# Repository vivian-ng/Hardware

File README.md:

# Hardware

Repository of all hardware related files, including schematics, gerber files, and related software.

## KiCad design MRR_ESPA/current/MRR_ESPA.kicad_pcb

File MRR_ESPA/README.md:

# MRR ESPA
## A basic 3D printer control board based on ESP32

This is a bare-minimum 3D printer control board based on the ESP32 microcontroller, which comes with built-in WiFi and BlueTooth.

**Work in progress! Do not attempt production using this schematic!**<br>
**Current version: v1.0**<br>
Note: As of v0.8, files have been migrated to KiCad so that the files can be more accessible to everyone who wishes to modify them.<br>

Features:
- Able to use up to 4 stepper drivers: X, Y, Z, and E0
- 12V to 24V input power supply
- Separate power supply for the heat bed
- X, Y, and Z min endstops
- Allows the use of a Z-axis probe, such as an inductive sensor, running on the input supply voltage (12V to 24V)
- AUX1 connector for use with an external host, such as the closed-source MKS TFT32 (**Untested!!**)
- Physical size of 99.5mm by 99.5mm. Mounting holes are 3.5mm in diameter, with centers 4mm from the edges.
- "BOOT" button can be used to reset the board.

# Firmware

Marlin 2.0 has added support for ESP32. This board was based on the initial pins definition used. <br>
In addition, [Luc](https://github.com/luc-github) has been working on a Marlin fork which incorporates part of his ESP3D webUI into Marlin itself.

## Flashing firmware

- You should be able to flash firmware through the USB port. Depending on your operating system, you may need to install drivers for the CH340. Please use Google or another search engine to find the right CH340 driver for your operating system.
- To flash firmware by directly connecting to TX/RX pins, you will need to connect IO0 to GND, then reboot (press "BOOT" button) to enter flash mode. After flashing the firmware, disconnect IO0 from GND, and press "BOOT" button again to reboot into normal mode.
- Use a baud rate of 115200.

# Pins

To be added

# License
Released under CERN Open Hardware Licence v1.2. See LICENSE.txt for details.

## Warning

- This product uses high currents which may cause fires. Use with caution.
- Do not use input voltages higher than 24V. Input current must not exceed 15A.
- Do not attempt to use more than 15A for the heated bed. While the MOSFET is capable of such currents, the connectors are not. If you need more than 15A, use an external MOSFET. In any case, it is highly recommended to use an external MOSFET for the heated bed to avoid drawing high currents through this product.
- Do not attempt to use more than 5A for the hot end. While the MOSFET is capable of such currents, the connectors are not. If you need more than 5A, use an external MOSFET.
- Do not reverse polarity.
- The breakout and endstop pins are rated for 3.3V, which is the voltage the ESP32 operates at. Attempting to feed inputs above 3.3V to these pins may damage the board.
- It is recommended to power the board only via USB (i.e. turn off PSU power supply) when flashing the board.

## Disclaimer

This product is provided as-is. While care has been taken to design a safe product, it is the user's responsibility to make sure precautions are taken to prevent damage or injury when using this product. This includes adhering to all warnings provided. By using this product, the user accepts responsibility to bear all liabilities from any damage or injury arising from the use of this product.

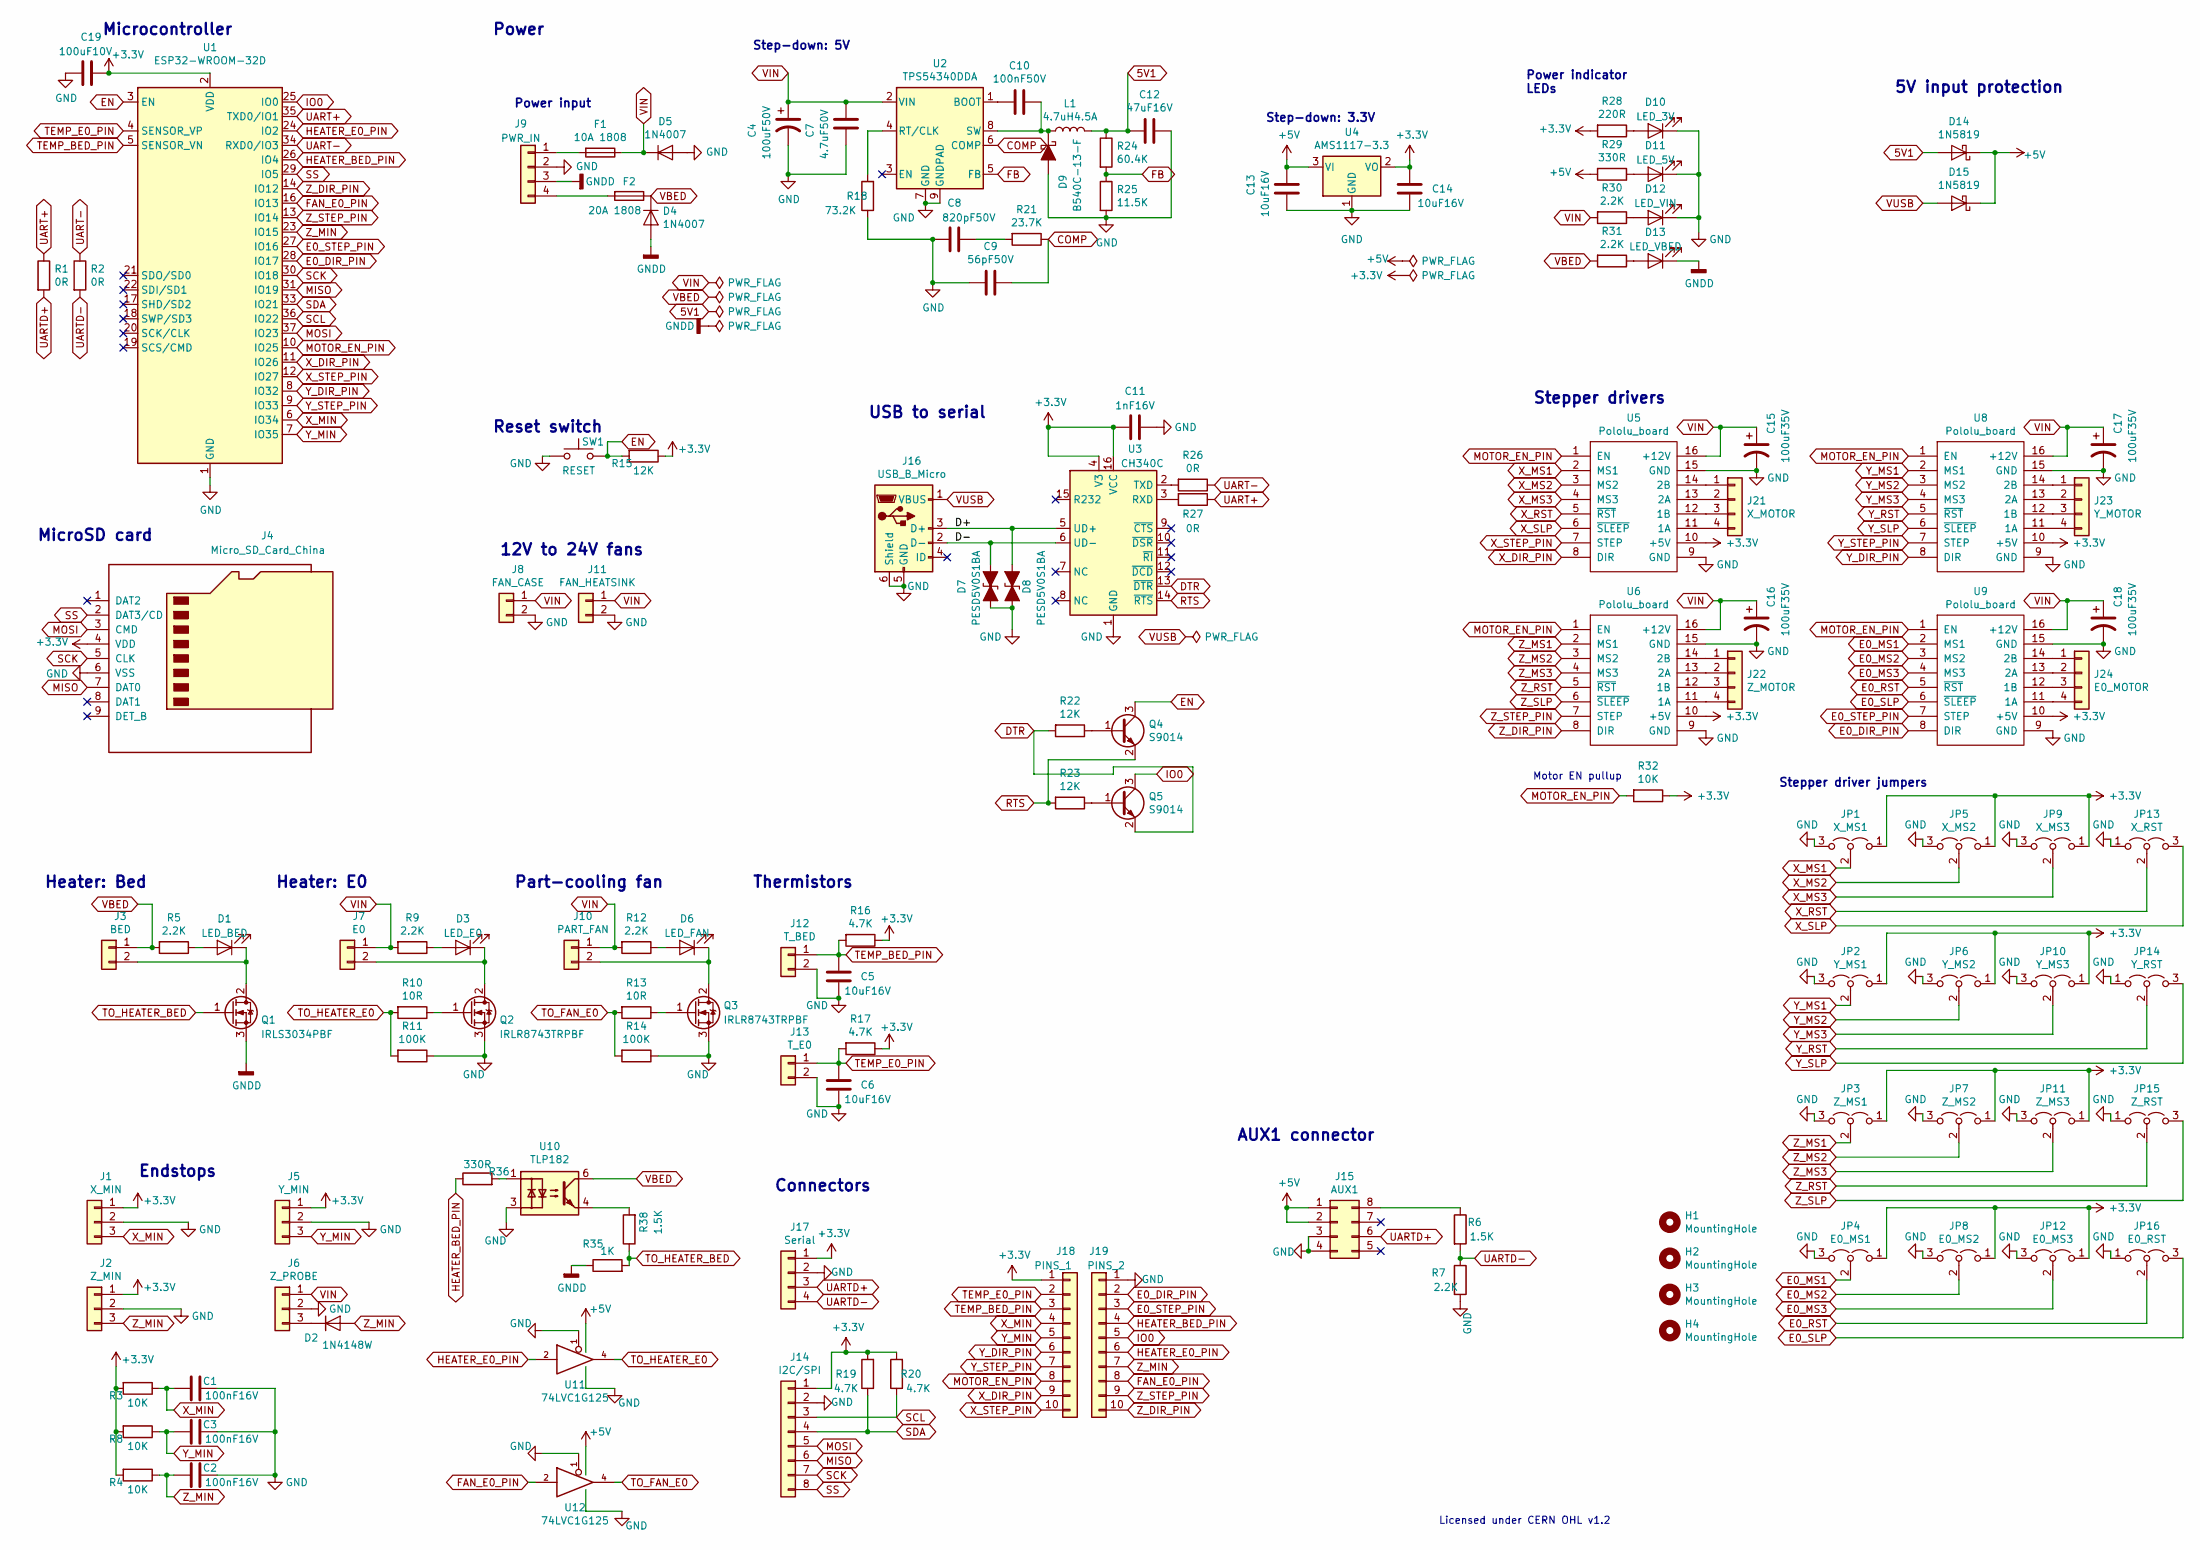
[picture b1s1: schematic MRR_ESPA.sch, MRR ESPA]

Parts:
C1, C2, C3: 100nF16V; C_0805_2012Metric
C4: 100uF50V; CP_Elec_8x10
C5, C6, C13, C14: 10uF16V; C_0805_2012Metric
C7: 4.7uF50V; C_1206_3216Metric
C8: 820pF50V; C_0805_2012Metric
C9: 56pF50V; C_0805_2012Metric
C10: 100nF50V; C_0805_2012Metric
C11: 1nF16V; C_0805_2012Metric
C12: 47uF16V; C_1206_3216Metric
C15, C16, C17, C18: 100uF35V; CP_Elec_6.3x7.7
C19: 100uF10V; C_1206_3216Metric
D1: LED_BED; LED_0805
D2: 1N4148W; D_SOD-123
D3: LED_E0; LED_0805
D4, D5: 1N4007; D_SOD-123F
D6: LED_FAN; LED_0805
D7, D8: PESD5V0S1BA; D_SOD-323
D9: B540C-13-F; D_SMC
D10: LED_3V; LED_0805
D11: LED_5V; LED_0805
D12: LED_VIN; LED_0805
D13: LED_VBED; LED_0805
D14, D15: 1N5819; D_SOD-123
F1: 10A 1808; Littelfuse_0451
F2: 20A 1808; Littelfuse_0451
H1, H2, H3, H4: MountingHole; MountingHole_3.2mm_M3_DIN965
J1: X_MIN; PinHeader_1x03_P2.54mm_Vertical
J2: Z_MIN; PinHeader_1x03_P2.54mm_Vertical
J3: BED; TerminalBlock_Phoenix_MKDS-3-2-5.08_1x02_P5.08mm_Horizontal
J4: Micro_SD_Card_China; Conn_uSDcard
J5: Y_MIN; PinHeader_1x03_P2.54mm_Vertical
J6: Z_PROBE; PinHeader_1x03_P2.54mm_Vertical
J7: E0; TerminalBlock_Phoenix_MKDS-1,5-2-5.08_1x02_P5.08mm_Horizont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
J8: FAN_CASE; PinHeader_1x02_P2.54mm_Vertical
J9: PWR_IN; TerminalBlock_Phoenix_MKDS-3-4-5.08_1x04_P5.08mm_Horizontal
J10: PART_FAN; PinHeader_1x02_P2.54mm_Vertical
J11: FAN_HEATSINK; PinHeader_1x02_P2.54mm_Vertical
J12: T_BED; PinHeader_1x02_P2.54mm_Vertical
J13: T_E0; PinHeader_1x02_P2.54mm_Vertical
J14: I2C/SPI; PinHeader_1x08_P2.54mm_Vertical
J15: AUX1; IDC-Header_2x04_P2.54mm_Vertical
J16: USB_B_Micro; USB_Micro-B_Molex-105017-0001
J17: Serial; PinHeader_1x04_P2.54mm_Vertical
J18: PINS_1; PinHeader_1x10_P2.54mm_Vertical
J19: PINS_2; PinHeader_1x10_P2.54mm_Vertical
J21: X_MOTOR; PinHeader_1x04_P2.54mm_Vertical
J22: Z_MOTOR; PinHeader_1x04_P2.54mm_Vertical
J23: Y_MOTOR; PinHeader_1x04_P2.54mm_Vertical
J24: E0_MOTOR; PinHeader_1x04_P2.54mm_Vertical
JP1: X_MS1; PinHeader_1x03_P2.54mm_Vertical
JP2: Y_MS1; PinHeader_1x03_P2.54mm_Vertical
JP3: Z_MS1; PinHeader_1x03_P2.54mm_Vertical
JP4: E0_MS1; PinHeader_1x03_P2.54mm_Vertical
JP5: X_MS2; PinHeader_1x03_P2.54mm_Vertical
JP6: Y_MS2; PinHeader_1x03_P2.54mm_Vertical
JP7: Z_MS2; PinHeader_1x03_P2.54mm_Vertical
JP8: E0_MS2; PinHeader_1x03_P2.54mm_Vertical
JP9: X_MS3; PinHeader_1x03_P2.54mm_Vertical
JP10: Y_MS3; PinHeader_1x03_P2.54mm_Vertical
JP11: Z_MS3; PinHeader_1x03_P2.54mm_Vertical
JP12: E0_MS3; PinHeader_1x03_P2.54mm_Vertical
JP13: X_RST; PinHeader_1x03_P2.54mm_Vertical
JP14: Y_RST; PinHeader_1x03_P2.54mm_Vertical
JP15: Z_RST; PinHeader_1x03_P2.54mm_Vertical
JP16: E0_RST; PinHeader_1x03_P2.54mm_Vertical
L1: 4.7uH4.5A; SMMS0530
Q1: IRLS3034PBF; TO-263-2
Q2, Q3: IRLR8743TRPBF; TO-252-2
Q4, Q5: S9014; SOT-23
R1, R2, R26, R27: 0R; R_0805_2012Metric
R3, R4, R8, R32: 10K; R_0805_2012Metric
R5, R7, R9, R12, R30, R31: 2.2K; R_0805_2012Metric
R6, R38: 1.5K; R_0805_2012Metric
R10, R13: 10R; R_0805_2012Metric
R11, R14: 100K; R_0805_2012Metric
R15, R22, R23: 12K; R_0805_2012Metric
R16, R17, R19, R20: 4.7K; R_0805_2012Metric
R18: 73.2K; R_0805_2012Metric
R21: 23.7K; R_0805_2012Metric
R24: 60.4K; R_0805_2012Metric
R25: 11.5K; R_0805_2012Metric
R28: 220R; R_0805_2012Metric
R29, R36: 330R; R_0805_2012Metric
R35: 1K; R_0805_2012Metric
SW1: RESET; 6x6mmTactileSwitch
U1: ESP32-WROOM-32D; ESP32-WROOM-32
U2: TPS54340DDA; TI_SO-PowerPAD-8_ThermalVias
U3: CH340C; SOIC-16_3.9x9.9mm_P1.27mm
U4: AMS1117-3.3; SOT-223-3_TabPin2
U5, U6, U8, U9: Pololu_board; Pololu_Breakout-16_15.2x20.3mm
U10: TLP182; MFSOP6-4_4.4x3.6mm_P1.27mm
U11, U12: 74LVC1G125; SOT-353_SC-70-5

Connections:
5V1: C12.2, D14.2 (A), L1.2, R24.1
+3V3: C11.2, C14.1, C19.1, J1.1, J2.1, J4.4 (VDD), J5.1, J14.1, J17.1, J18.1, JP1.1 (A), JP2.1 (A), JP3.1 (A), JP4.1 (A), JP5.1 (A), JP6.1 (A), JP7.1 (A), JP8.1 (A), JP9.1 (A), JP10.1 (A), JP11.1 (A), JP12.1 (A), R3.2, R4.2, R8.2, R15.1, R16.1, R17.1, R19.2, R20.2, R28.2, R32.1, U1.2 (VDD), U3.4 (V3), U3.16 (VCC), U4.2 (VO), U5.10 (+5V), U6.10 (+5V), U8.10 (+5V), U9.10 (+5V)
+5V: C13.1, D14.1 (K), D15.1 (K), J15.1, J15.2, R29.2, U4.3 (VI), U11.5 (VCC), U12.5 (VCC)
/D+: D8.1 (A1), J16.3 (D+), U3.5 (UD+)
/D-: D7.1 (A1), J16.2 (D-), U3.6 (UD-)
COMP: C9.1, R21.1, U2.6 (COMP)
DTR: Q5.2 (E), R22.2, U3.13 (~DTR)
E0_DIR_PIN: J19.2, U1.28 (IO17), U9.8 (DIR)
E0_MS1: JP4.2 (C), U9.2 (MS1)
E0_MS2: JP8.2 (C), U9.3 (MS2)
E0_MS3: JP12.2 (C), U9.4 (MS3)
E0_RST: JP16.2 (C), U9.5 (~RST)
E0_SLP: JP16.3 (B), U9.6 (~SLEEP)
E0_STEP_PIN: J19.3, U1.27 (IO16), U9.7 (STEP)
EN: Q4.3 (C), R15.2, SW1.2, U1.3 (EN)
FAN_E0_PIN: J19.8, U1.16 (IO13), U12.2
FB: R24.2, R25.1, U2.5 (FB)
GND: C1.1, C2.1, C3.1, C4.2, C5.1, C6.1, C7.1, C8.2, C9.2, C11.1, C12.1, C13.2, C14.2, C15.2, C16.2, C17.2, C18.2, C19.2, D5.2 (A), D7.2 (A2), D8.2 (A2), D9.2 (A), D10.1 (K), D11.1 (K), D12.1 (K), J1.2, J2.2, J4.6 (VSS), J5.2, J6.2, J8.2, J9.2, J11.2, J12.2, J13.2, J14.2, J15.3, J15.4, J16.5 (GND), J16.6 (Shield), J17.2, J19.1, JP1.3 (B), JP2.3 (B), JP3.3 (B), JP4.3 (B), JP5.3 (B), JP6.3 (B), JP7.3 (B), JP8.3 (B), JP9.3 (B), JP10.3 (B), JP11.3 (B), JP12.3 (B), JP13.1 (A), JP14.1 (A), JP15.1 (A), JP16.1 (A), Q2.3 (S), Q3.3 (S), R7.2, R11.1, R14.1, R18.1, R25.2, SW1.1, U1.1 (GND), U1.15 (GND), U1.38 (GND), U1.39, U2.7 (GND), U2.9 (GNDPAD), U3.1 (GND), U4.1 (GND), U5.9 (GND), U5.15 (GND), U6.9 (GND), U6.15 (GND), U8.9 (GND), U8.15 (GND), U9.9 (GND), U9.15 (GND), U10.3, U11.1, U11.3 (GND), U12.1, U12.3 (GND)
GNDD: D4.2 (A), D13.1 (K), J9.3, Q1.3 (S), R35.1
HEATER_BED_PIN: J19.4, R36.1, U1.26 (IO4)
HEATER_E0_PIN: J19.6, U1.24 (IO2), U11.2
IO0: J19.5, Q5.3 (C), U1.25 (IO0)
MISO: J4.7 (DAT0), J14.6, U1.31 (IO19)
MOSI: J4.3 (CMD), J14.5, U1.37 (IO23)
MOTOR_EN_PIN: J18.8, R32.2, U1.10 (IO25), U5.1 (EN), U6.1 (EN), U8.1 (EN), U9.1 (EN)
unnamed: C8.1, R21.2
unnamed: C10.1, D9.1 (K), L1.1, U2.8 (SW)
unnamed: C10.2, U2.1 (BOOT)
unnamed: D1.1 (K), J3.2, Q1.2 (D)
unnamed: D1.2 (A), R5.1
unnamed: D2.1 (K), J6.3
unnamed: D3.1 (K), J7.2, Q2.2 (D)
unnamed: D3.2 (A), R9.1
unnamed: D6.1 (K), J10.2, Q3.2 (D)
unnamed: D6.2 (A), R12.1
unnamed: D10.2 (A), R28.1
unnamed: D11.2 (A), R29.1
unnamed: D12.2 (A), R30.1
unnamed: D13.2 (A), R31.1
unnamed: F1.2, J9.1
unnamed: F2.2, J9.4
unnamed: J15.8, R6.1
unnamed: J21.1, U5.14 (2B)
unnamed: J21.2, U5.13 (2A)
unnamed: J21.3, U5.12 (1B)
unnamed: J21.4, U5.11 (1A)
unnamed: J22.1, U6.14 (2B)
unnamed: J22.2, U6.13 (2A)
unnamed: J22.3, U6.12 (1B)
unnamed: J22.4, U6.11 (1A)
unnamed: J23.1, U8.14 (2B)
unnamed: J23.2, U8.13 (2A)
unnamed: J23.3, U8.12 (1B)
unnamed: J23.4, U8.11 (1A)
unnamed: J24.1, U9.14 (2B)
unnamed: J24.2, U9.13 (2A)
unnamed: J24.3, U9.12 (1B)
unnamed: J24.4, U9.11 (1A)
unnamed: Q2.1 (G), R10.1
unnamed: Q3.1 (G), R13.1
unnamed: Q4.1 (B), R22.1
unnamed: Q5.1 (B), R23.1
unnamed: R18.2, U2.4 (RT/CLK)
unnamed: R26.2, U3.2 (TXD)
unnamed: R27.2, U3.3 (RXD)
unnamed: R36.2, U10.1
unnamed: R38.2, U10.4
RTS: Q4.2 (E), R23.2, U3.14 (~RTS)
SCK: J4.5 (CLK), J14.7, U1.30 (IO18)
SCL: J14.3, R20.1, U1.36 (IO22)
SDA: J14.4, R19.1, U1.33 (IO21)
SS: J4.2 (DAT3/CD), J14.8, U1.29 (IO5)
TEMP_BED_PIN: C5.2, J12.1, J18.3, R16.2, U1.5 (SENSOR_VN)
TEMP_E0_PIN: C6.2, J13.1, J18.2, R17.2, U1.4 (SENSOR_VP)
TO_FAN_E0: R13.2, R14.2, U12.4
TO_HEATER_BED: Q1.1 (G), R35.2, R38.1
TO_HEATER_E0: R10.2, R11.2, U11.4
UART+: R1.1, R27.1, U1.35 (TXD0/IO1)
UART-: R2.1, R26.1, U1.34 (RXD0/IO3)
UARTD+: J15.6, J17.3, R1.2
UARTD-: J17.4, R2.2, R6.2, R7.1
VBED: D4.1 (K), F2.1, J3.1, R5.2, R31.2, U10.6
VIN: C4.1, C7.2, C15.1, C16.1, C17.1, C18.1, D5.1 (K), F1.1, J6.1, J7.1, J8.1, J10.1, J11.1, R9.2, R12.2, R30.2, U2.2 (VIN), U5.16 (+12V), U6.16 (+12V), U8.16 (+12V), U9.16 (+12V)
VUSB: D15.2 (A), J16.1 (VBUS)
X_DIR_PIN: J18.9, U1.11 (IO26), U5.8 (DIR)
X_MIN: C1.2, J1.3, J18.4, R3.1, U1.6 (IO34)
X_MS1: JP1.2 (C), U5.2 (MS1)
X_MS2: JP5.2 (C), U5.3 (MS2)
X_MS3: JP9.2 (C), U5.4 (MS3)
X_RST: JP13.2 (C), U5.5 (~RST)
X_SLP: JP13.3 (B), U5.6 (~SLEEP)
X_STEP_PIN: J18.10, U1.12 (IO27), U5.7 (STEP)
Y_DIR_PIN: J18.6, U1.8 (IO32), U8.8 (DIR)
Y_MIN: C3.2, J5.3, J18.5, R8.1, U1.7 (IO35)
Y_MS1: JP2.2 (C), U8.2 (MS1)
Y_MS2: JP6.2 (C), U8.3 (MS2)
Y_MS3: JP10.2 (C), U8.4 (MS3)
Y_RST: JP14.2 (C), U8.5 (~RST)
Y_SLP: JP14.3 (B), U8.6 (~SLEEP)
Y_STEP_PIN: J18.7, U1.9 (IO33), U8.7 (STEP)
Z_DIR_PIN: J19.10, U1.14 (IO12), U6.8 (DIR)
Z_MIN: C2.2, D2.2 (A), J2.3, J19.7, R4.1, U1.23 (IO15)
Z_MS1: JP3.2 (C), U6.2 (MS1)
Z_MS2: JP7.2 (C), U6.3 (MS2)
Z_MS3: JP11.2 (C), U6.4 (MS3)
Z_RST: JP15.2 (C), U6.5 (~RST)
Z_SLP: JP15.3 (B), U6.6 (~SLEEP)
Z_STEP_PIN: J19.9, U1.13 (IO14), U6.7 (STEP)

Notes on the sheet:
Microcontroller
MicroSD card
Power
Step-down: 5V
Step-down: 3.3V
Power indicator LEDs
Power input
USB to serial
5V input protection
Heater: Bed
Heater: E0
Part-cooling fan
Motor EN pullup
Stepper drivers
12V to 24V fans
Thermistors
Endstops
Reset switch
Connectors
Stepper driver jumpers
Licensed under CERN OHL v1.2
AUX1 connector

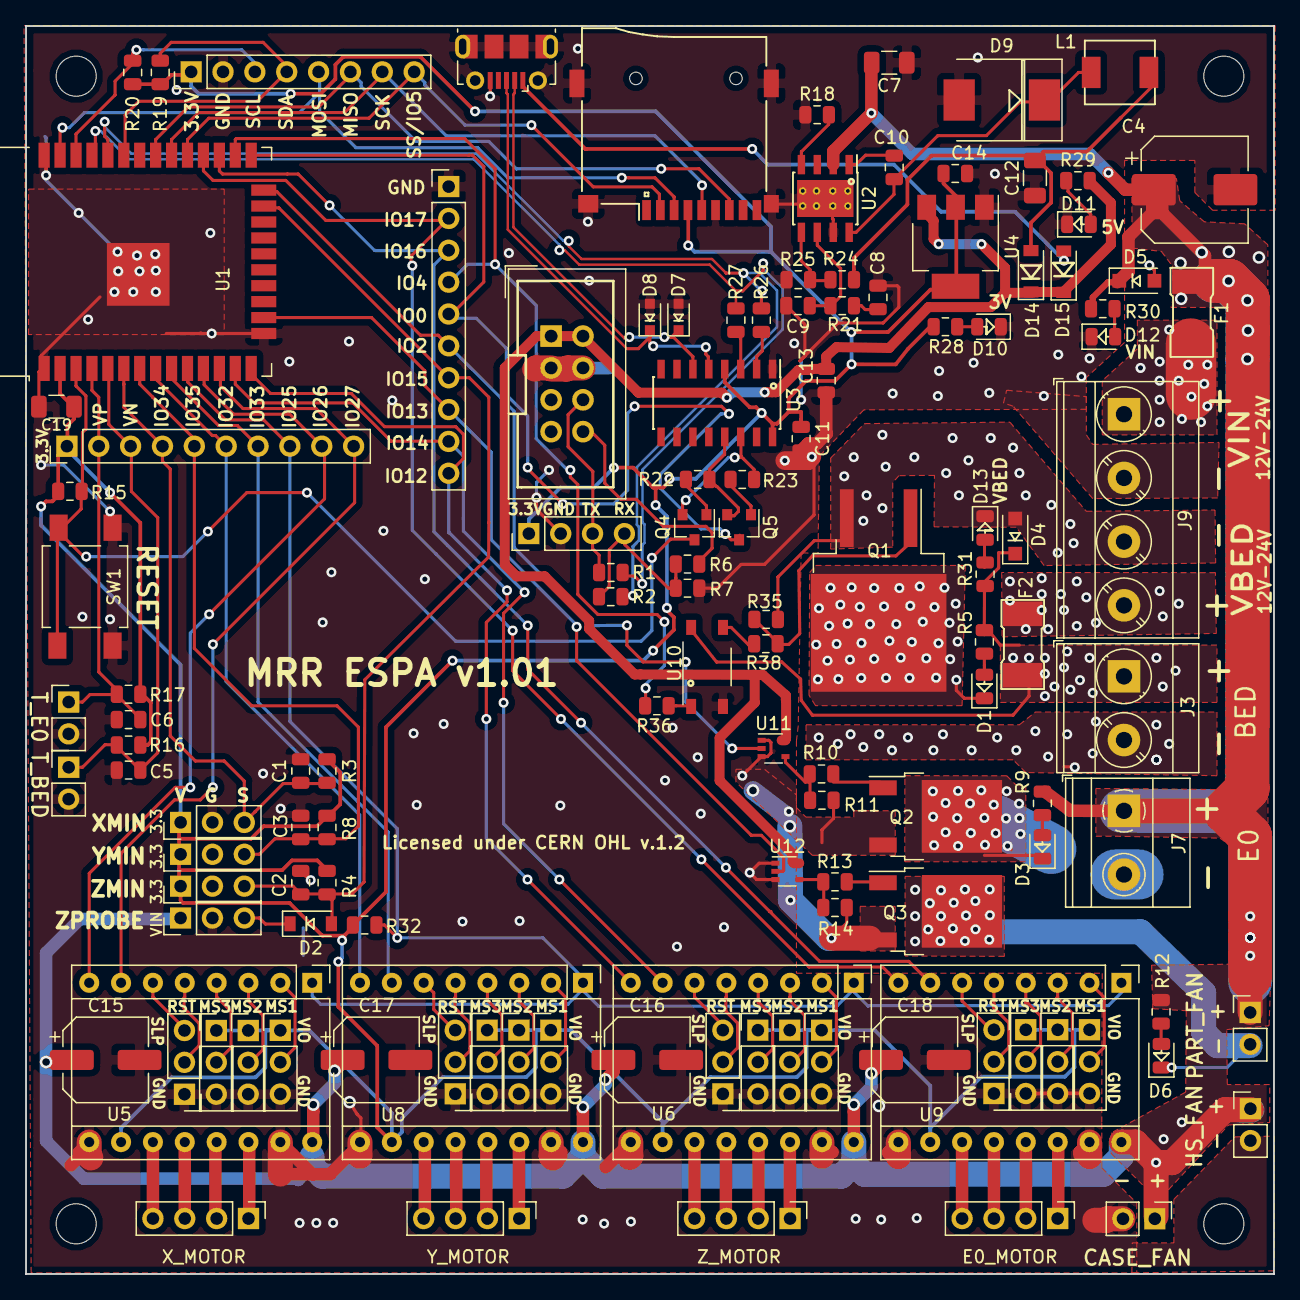
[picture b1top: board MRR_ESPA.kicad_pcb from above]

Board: 2 copper layers, 99.5 x 99.5 mm, 132 parts (0 on the bottom side), 108 nets.

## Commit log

2018-12-09 Added schematic MRR_ESP_3DP
2018-12-10 Added LICENSE.txt
2018-12-10 Added cern howto
2018-12-12 Add STM32F4 shield
2018-12-12 Add gerber file for v0.4
2018-12-13 Update copper area
2018-12-13 Rename PCB_ESP32_3DP_v3.pcbdoc to PCB_MRR_ESP_3DP_v0.4.pcbdoc
2018-12-15 Add v0.5
2018-12-15 Move to v0.4 folder
2018-12-17 Update PCB letter size
2018-12-17 Move v0.5 files to v0.5 folder
2018-12-18 Add v0.6 files
2018-12-18 Connected 74HCT02 GND pin
2018-12-18 Changed R13 value
2018-12-20 Minor change to PCB
2019-01-11 Moved v0.6 files to v0.6 folder
2019-01-11 Added v0.7 files
2019-01-11 Added v0.7 BOM
2019-01-11 Minor change to v0,7
2019-01-28 Renamed MRR_ESP32_3DP to MRR_ESPA
2019-01-31 Moved v0.7 files
2019-01-31 Added v0.8 files
2019-03-11 Added v0.9
2019-04-17 Added v1.0
2019-05-18 Added macros
2019-06-20 Added macrocfg.json
